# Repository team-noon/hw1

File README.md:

# Hardware 1
The first hardware design of our team

> [!WARNING]
> still under development!

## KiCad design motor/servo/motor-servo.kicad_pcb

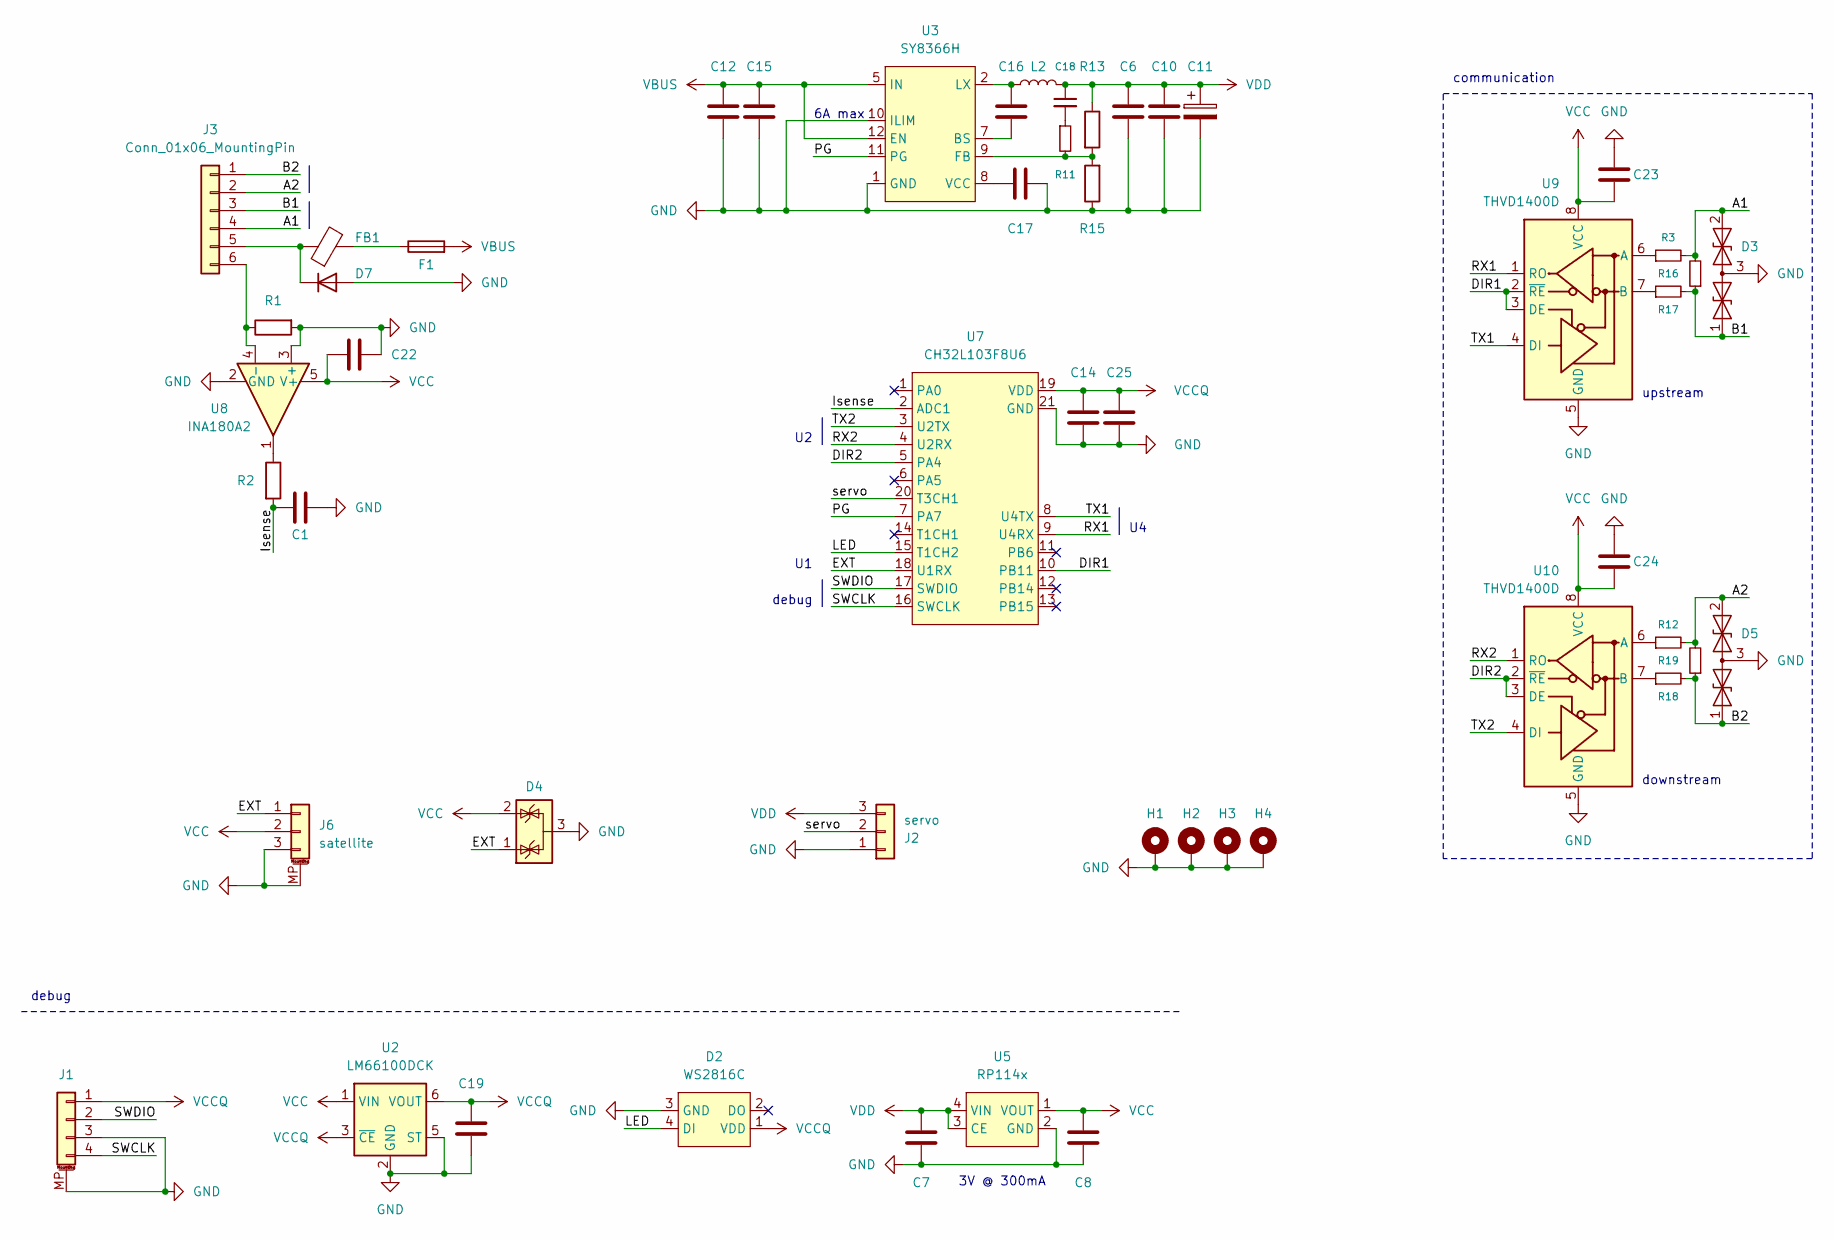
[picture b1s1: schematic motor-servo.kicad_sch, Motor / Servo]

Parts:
C1: 100n
C6, C10: 22u; C_0805_2012Metric; LCSC C98190
C7, C8: 1u; C_0402_1005Metric; LCSC C7001784
C11: 220u; CP_Elec_6.3x5.4; LCSC C2977551
C12: 10u (HV); C_0805_2012Metric
C14: 100n; C_0402_1005Metric; LCSC C77020
C15: 1u (HV); C_0603_1608Metric; LCSC C307331
C16: 100n; C_0402_1005Metric; LCSC C60474
C17: 2.2u; C_0402_1005Metric; LCSC C12530
C18: 22p; C_0402_1005Metric; LCSC C106203
C19: 10u; C_0402_1005Metric; LCSC C315248
C22, C23, C24: 100n; C_0402_1005Metric
C25: 2.2u; C_0402_1005Metric; LCSC C77020
D2: WS2816C; WS2816C-1313-4P; LCSC C42417612
D3, D5: SM712_SOT23; SOT-23; LCSC C404012
D4: NUP1303; SOT-23; LCSC C2831529
D7: D; D_SOD-123F; LCSC C19077515
F1: 8A; Fuse_1206_3216Metric; LCSC C41367232
FB1: FerriteBead; L_0805_2012Metric; LCSC C596496
H1, H2, H3, H4: MountingHole_Pad; MountingHole_2.2mm_M2_DIN965_Pad
J1: DEBUG; JST_SH_BM04B-SRSS-TB_1x04-1MP_P1.00mm_Vertical; LCSC C160390
J2: servo; Molex_Micro-Fit_3.0_43650-0300_1x03_P3.00mm_Horizontal; LCSC C503478
J3: Conn_01x06_MountingPin; Molex_Micro-Fit_3.0_43650-0600_1x06_P3.00mm_Horizontal; LCSC C492352
J6: satellite; JST_SH_SM03B-SRSS-TB_1x03-1MP_P1.00mm_Horizontal; LCSC C160403
L2: 2u; 0630CDMCD_DS; LCSC C2453290
R1: 10m; R_1206_3216Metric; LCSC C7467248
R2: 100
R3, R12, R16, R17, R18, R19: R_Small; R_0402_1005Metric
R11: 150k; R_0402_1005Metric
R13: 100k; R_0402_1005Metric
R15: 13k; R_0402_1005Metric
U2: LM66100DCK; SOT-363_SC-70-6; LCSC C2869734
U3: SY8366H; QFN3x3-12; LCSC C178253
U5: RP114x; UDFN-4-1EP_1x1mm_P0.65mm_EP0.48x0.48mm; LCSC C194610
U7: CH32L103F8U6; VQFN-20-1EP_3x3mm_P0.4mm_EP1.7x1.7mm; LCSC C22467836
U8: INA180A2; SOT-23-5; LCSC C192764
U9, U10: THVD1400D; SOT-583-8; LCSC C3235289

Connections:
/A1: D3.2 (A2), J3.4, R3.2, R16.2
/A2: D5.2 (A2), J3.2, R12.2, R19.2
/B1: D3.1 (A1), J3.3, R16.1, R17.2
/B2: D5.1 (A1), J3.1, R18.2, R19.1
/DIR1: U7.10 (PB11), U9.2 (~RE), U9.3 (DE)
/DIR2: U7.5 (PA4), U10.2 (~RE), U10.3 (DE)
/EXT: D4.1 (K), J6.1, U7.18 (U1RX)
/Isense: C1.1, R2.2, U7.2 (ADC1)
/LED: D2.4 (DI), U7.15 (T1CH2)
/PG: U3.11 (PG), U7.7 (PA7)
/RX1: U7.9 (U4RX), U9.1 (RO)
/RX2: U7.4 (U2RX), U10.1 (RO)
/SWCLK: J1.4, U7.16 (SWCLK)
/SWDIO: J1.2, U7.17 (SWDIO)
/TX1: U7.8 (U4TX), U9.4 (DI)
/TX2: U7.3 (U2TX), U10.4 (DI)
/servo: J2.2, U7.20 (T3CH1)
GND: C1.2, C6.2, C7.2, C8.2, C10.2, C11.2, C12.2, C14.2, C15.2, C17.2, C19.2, C22.2, C23.1, C24.1, C25.2, D2.3 (GND), D3.3 (common), D4.3 (A), D5.3 (common), D7.2 (A), H1.1 (1_1), H2.1 (1_1), H3.1 (1_1), H4.1 (1_1), J1.3, J1.MP (MountPin), J2.1, J6.3, J6.MP (MountPin), R1.2, R15.1, U2.2 (GND), U2.5 (ST), U3.1 (GND), U3.10 (ILIM), U5.2 (GND), U5.5 (EP), U7.21 (GND), U8.2 (GND), U8.3 (+), U9.5 (GND), U10.5 (GND)
unnamed: C18.2, R11.1
unnamed: D7.1 (K), FB1.1, J3.5
unnamed: F1.1, FB1.2
unnamed: J3.6, R1.1, U8.4 (-)
unnamed: R2.1, U8.1
unnamed: C16.1, U3.7 (BS)
unnamed: R11.2, R13.2, R15.2, U3.9 (FB)
unnamed: C16.2, L2.1, U3.2 (LX)
unnamed: C17.1, U3.8 (VCC)
unnamed: R3.1, U9.6 (A)
unnamed: R17.1, U9.7 (B)
unnamed: R12.1, U10.6 (A)
unnamed: R18.1, U10.7 (B)
VBUS: C12.1, C15.1, F1.2, U3.5 (IN), U3.6 (IN), U3.12 (EN)
VCC: C8.1, C22.1, C23.2, C24.2, D4.2 (K), J6.2, U2.1 (VIN), U5.1 (VOUT), U8.5 (V+), U9.8 (VCC), U10.8 (VCC)
VCCQ: C14.1, C19.1, C25.1, D2.1 (VDD), J1.1, U2.3 (~CE), U2.6 (VOUT), U7.19 (VDD)
VDD: C6.1, C7.1, C10.1, C11.1, C18.1, J2.3, L2.2, R13.1, U5.3 (CE), U5.4 (VIN)

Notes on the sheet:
3V @ 300mA
downstream
debug
6A max
upstream
communication

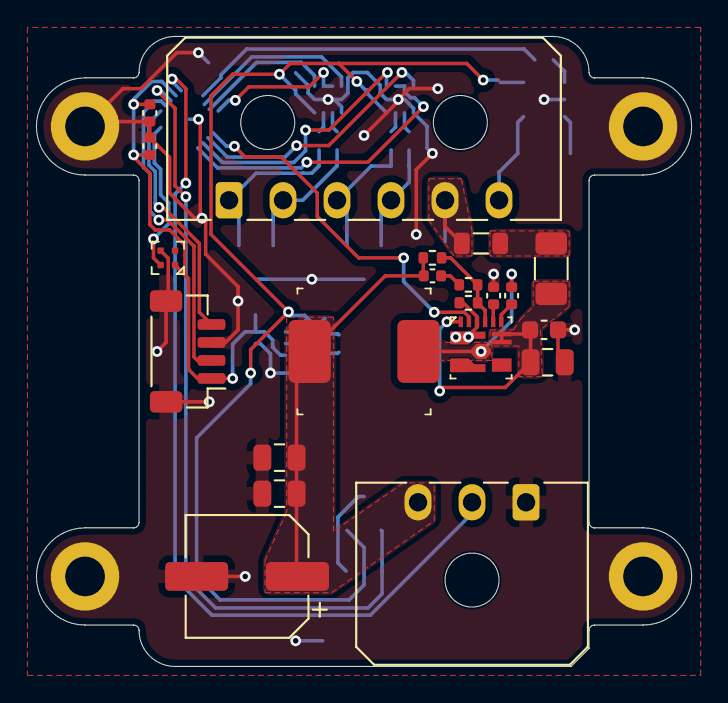
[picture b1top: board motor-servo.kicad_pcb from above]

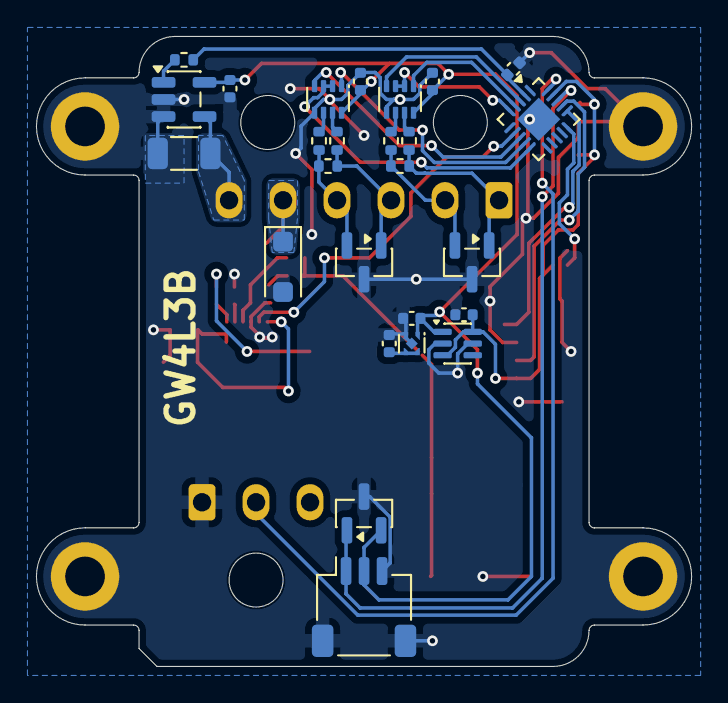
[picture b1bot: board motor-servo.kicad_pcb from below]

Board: 2 copper layers, 36.4 x 35.0 mm, 51 parts (26 on the bottom side), 35 nets.

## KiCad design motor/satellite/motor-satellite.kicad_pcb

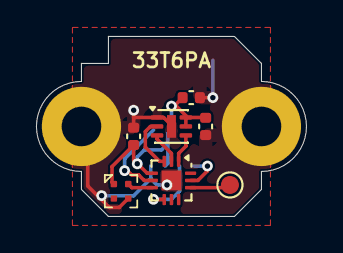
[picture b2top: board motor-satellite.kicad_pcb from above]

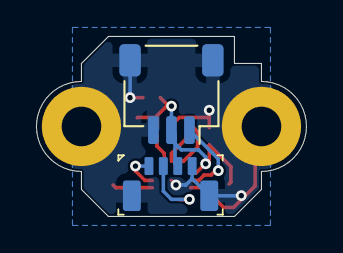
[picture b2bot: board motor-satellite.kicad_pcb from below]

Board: 2 copper layers, 15.0 x 10.0 mm, 11 parts (2 on the bottom side), 10 nets.

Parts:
C1, C2: 100n; C_0402_1005Metric
C3: 10u; C_0402_1005Metric
D2: WS2816C; WS2816C-1313-4P
H1, H2: MountingScrew; MountingHole_2.2mm_M2_Pad
J3: Conn_01x04_MountingPin; HC-0.8-4PWT
J6: Conn_01x03_MountingPin; JST_SH_SM03B-SRSS-TB_1x03-1MP_P1.00mm_Horizontal
TP1: SWIO; TestPoint_Pad_D1.0mm
U1: CH32V005D6U6; UQFN-12-1EP_2x2mm_P0.4mm_EP1.1x1.1mm
U3: SC4251; MLF-6-1EP_1.6x1.6mm_P0.5mm_EP0.5x1.26mm

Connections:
/A0: J3.2, U1.7 (PC4)
/A1: J3.1, U1.11 (PD4)
/LED: D2.4 (DI), U1.6 (PC3)
/PX: U1.2 (PA2), U3.3 (OUTx)
/PY: U1.1 (PA1), U3.4 (OUTy)
/SLEEP: U1.3 (PD0), U3.2 (SLEEP)
/TX: J6.1, U1.5 (PC0)
GND: C1.2, C2.2, C3.2, D2.3 (GND), H1.1 (PAD_1), H2.1 (PAD_1), J3.4, J3.MP (MountPin), J6.3, J6.MP (MountPin), U1.13 (VSS), U3.1 (GND), U3.7 (EP)
unnamed: TP1.1 (1_1), U1.10 (SWIO)
VCC: C1.1, C2.1, C3.1, D2.1 (VDD), J3.3, J6.2, U1.4 (VDD), U3.5 (GAIN), U3.6 (VCC)

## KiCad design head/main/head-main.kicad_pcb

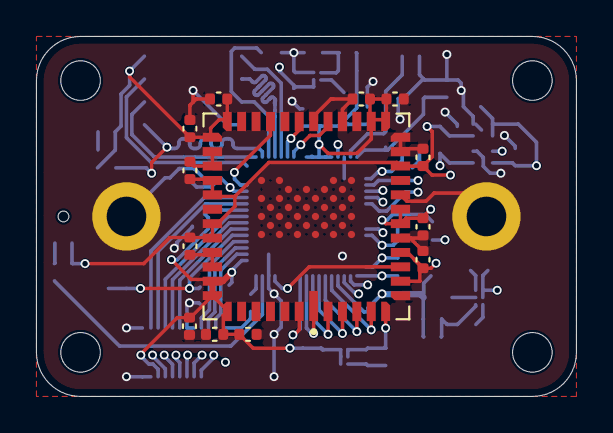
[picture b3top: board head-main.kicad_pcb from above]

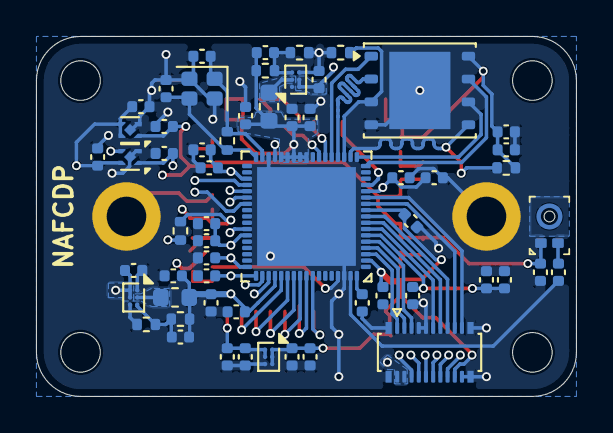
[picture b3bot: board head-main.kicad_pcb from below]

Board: 4 copper layers, 30.0 x 20.0 mm, 77 parts (60 on the bottom side), 48 nets.

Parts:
C1, C2, C3, C4, C8, C9, C11, C15, C19, C22, C24, C27, C29, C31, C41, C43: 0.1u; C_0402_1005Metric
C5, C32, C39, C40, C60, C61, C65: 10u; C_0402_1005Metric
C6, C17, C20, C23, C33, C34, C37: 2.2u; C_0402_1005Metric
C7, C10, C26, C28, C30, C35, C36, C42, C50, C53, C54, C55: 1u; C_0402_1005Metric
C14: 100n; C_0402_1005Metric
C21, C25: 18p; C_0402_1005Metric
C51, C52: 4.7u; C_0402_1005Metric
C57: 47p; C_0402_1005Metric
C58: 33p; C_0402_1005Metric
C63: 4.7u (Cin); C_0402_1005Metric
H1, H2, H3, H4: MountingHole_Pad; MountingHole_2.2mm_M2
H5, H6: MountingHole_Pad; MountingHole_2.2mm_M2_DIN965_Pad
J1: conn_head_comms; Hirose_DF40C-20DP-0.4V_2x10-1MP_P0.4mm
L1, L2: 0.47u; L_0603_1608Metric
R1: 10k; R_0402_1005Metric
R3: 1M; R_0402_1005Metric
R4, R5: 4.7k; R_0402_1005Metric
R6, R7: 220k; R_0402_1005Metric
R9: 110k; R_0402_1005Metric
R10: 440k; R_0402_1005Metric
U1: CV1800B; ArtInChip_QFN-68-1EP_7x7mm_P0.35mm_EP5.49x5.49mm
U2: AR0237CS; PLCC-48-11.43x11.4mm
U3: GTA2718B-3HA
U4: W25Q128JVP; WSON-8-1EP_6x5mm_P1.27mm_EP3.4x4.3mm
U5, U6: RP509x; WLCSP-6_1.4x1.0mm_P0.4mm
U7: RP114x; UDFN-4-1EP_1x1mm_P0.65mm_EP0.48x0.48mm
U8: LP3982S; UDFN-4-1EP_1x1mm_P0.65mm_EP0.48x0.48mm
U9: NCP136; WLCSP-6_1.4x1.0mm_P0.4mm
Y1: 25M; Crystal_SMD_2016-4Pin_2.0x1.6mm

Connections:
+1V8: C1.1, C2.1, C4.1, C5.1, C6.1, C9.1, C10.1, C11.1, C14.1, C27.1, C31.1, C32.1, C34.1, C35.1, C37.1, C41.2, C58.2, C61.1, C63.1, J1.18, L2.2, R1.2, R4.2, R10.2, U1.2 (VDD18A_AUD), U1.10 (VDDIO_SD0_SPI), U1.26 (VDDQ), U1.27 (VDDQ), U1.28 (VDDQ), U1.29 (VDDIO_RTC), U1.30 (PWR_VBAT_DET), U1.52 (VDD18A_USB_PLL_ETH_CSI), U2.12 (VDDIO), U2.13 (VDD), U2.19 (VDD), U2.20 (VDDIO), U2.30 (VDDIO), U2.31 (VDD), U2.41 (VDD), U2.42 (VDDIO), U2.43 (VDD1V8_PHY), U4.8 (VCC), U9.A1 (IN), U9.B1 (EN), U9.C1 (BIAS)
+2V8: C26.1, C28.1, C30.1, C36.1, C43.1, C55.1, U2.8 (VDD_PLL), U2.10 (VAA), U2.16 (VAA), U2.34 (VAA_PIX), U2.35 (VAA), U2.37 (VAA), U2.38 (VAA_PIX), U3.1 (VDD), U8.1 (VOUT)
+3V3: C3.1, C53.1, U1.51 (VD33A_ETH_USB_SD1), U7.1 (VOUT)
+5V: C50.1, C51.1, C52.1, C54.1, J1.2, J1.4, U5.A2 (VIN), U5.B2 (CE), U6.A2 (VIN), U6.B2 (CE), U7.4 (VIN), U8.3 (EN), U8.4 (VIN)
/0V4: C29.2, C65.1, U2.6 (VDD_SLVS), U9.A2 (OUT), U9.B2 (SNS)
/0V9: C8.1, C15.1, C17.1, C19.1, C20.1, C22.1, C23.1, C24.1, C33.1, C39.1, C40.1, C57.2, C60.1, L1.2, R9.2, U1.6 (VDDC), U1.13 (VDDC), U1.37 (VDDC), U1.46 (VDDC), U1.55 (VDDC)
/CAM_CLK: U1.65 (MIPIRX0P), U2.9 (EXTCLK)
/CAM_OE: U1.14 (SPK_EN), U2.27 (OE_N)
/CAM_SCL: U1.23 (IIC0_SCL), U2.25 (SCL)
/CAM_SDA: U1.24 (IIC0_SDA), U2.23 (SDA)
/LED: J1.10, U1.41 (SD1_D0)
/MCN: U1.60 (MIPIRX2N), U2.1 (SLVSLCN)
/MCP: U1.61 (MIPIRX2P), U2.48 (SLVSLCP)
/MDN0: U1.56 (MIPIRX4N), U2.5 (SLVS0N)
/MDN1: U1.58 (MIPIRX3N), U2.3 (SPVS1N)
/MDP0: U1.57 (MIPIRX4P), U2.4 (SLVS0P)
/MDP1: U1.59 (MIPIRX3P), U2.2 (SLVS1P)
/MIC: C42.2, U3.2 (Out)
/NOR_CS: U1.22 (SPINOR_CS_X), U4.1 (~CS)
/NOR_HOLD: U1.17 (SPINOR_HOLD_X), U4.7 (~HOLD/~RESET/IO_{3})
/NOR_MISO: U1.21 (SPINOR_MISO), U4.2 (DO/IO_{1})
/NOR_MOSI: R4.1, U1.19 (SPINOR_MOSI), U4.5 (DI/IO_{0})
/NOR_SCK: U1.18 (SPINOR_SCK), U4.6 (CLK)
/NOR_WP: R5.1, U1.20 (SPINOR_WP_X), U4.3 (~WP/IO_{2})
/PWRSEQ: U1.31 (PWR_SEQ2), U7.3 (CE)
/U3RX: J1.12, U1.40 (SD1_D1)
/U3TX: J1.14, U1.39 (SD1_D2)
/UDIR: J1.16, U1.38 (SD1_D3)
/USB_DM: J1.6, U1.54 (USB_DM)
/USB_DP: J1.8, U1.53 (USB_DP)
/WIFI_CLK: J1.1, U1.3 (SD0_CLK)
/WIFI_CMD: J1.3, U1.4 (SD0_CMD)
/WIFI_D0: J1.5, U1.5 (SD0_D0)
/WIFI_D1: J1.11, U1.7 (SD0_D1)
/WIFI_D2: J1.13, U1.8 (SD0_D2)
/WIFI_D3: J1.15, U1.9 (SD0_D3)
/WIFI_EN: J1.19, U1.12 (SD0_PWR_EN)
/WIFI_INT: J1.17, U1.11 (SD0_CD)
/XIN: C25.2, R3.1, U1.33 (XTAL_XIN), Y1.1
/XOUT: C21.2, R3.2, U1.34 (XTAL_XOUT), Y1.3
GND: C1.2, C2.2, C3.2, C4.2, C5.2, C6.2, C7.2, C8.2, C9.2, C10.2, C11.2, C14.2, C15.2, C17.2, C19.2, C20.2, C21.1, C22.2, C23.2, C24.2, C25.1, C26.2, C27.2, C28.2, C29.1, C30.2, C31.2, C32.2, C33.2, C34.2, C35.2, C36.2, C37.2, C39.2, C40.2, C41.1, C43.2, C50.2, C51.2, C52.2, C53.2, C54.2, C55.2, C60.2, C61.2, C63.2, C65.2, H5.1 (1_1), H6.1 (1_1), J1.7, J1.9, J1.20, J1.MP (MountPin), R5.2, R6.1, R7.1, U1.32 (PTEST), U1.66 (VSS18A_AUD), U1.69 (VSSC), U2.7 (DGND), U2.11 (AGND), U2.14 (DGND), U2.17 (AGND), U2.18 (DGND), U2.22 (TEST), U2.24 (SADDR), U2.32 (DGND), U2.33 (AGND), U2.39 (AGND), U2.40 (DGND), U2.49 (DGND), U3.3 (GND), U4.4 (GND), U4.9 (EP), U5.A1 (MODE), U5.C2 (GND), U6.A1 (MODE), U6.C2 (GND), U7.2 (GND), U7.5 (TP), U8.2 (GND), U8.5 (TP), U9.C2 (GND), Y1.2 (G), Y1.4 (G)
unnamed: R1.1, U1.45 (USB_VBUS_DET)
unnamed: C42.1, U1.67 (PAD_AUD_AINL_MIC)
unnamed: C7.1, U1.68 (PAD_AUD_AVREF)
unnamed: L1.1, U5.B1 (LX)
unnamed: C57.1, R6.2, R9.1, U5.C1 (VFB)
unnamed: L2.1, U6.B1 (LX)
unnamed: C58.1, R7.2, R10.1, U6.C1 (VFB)

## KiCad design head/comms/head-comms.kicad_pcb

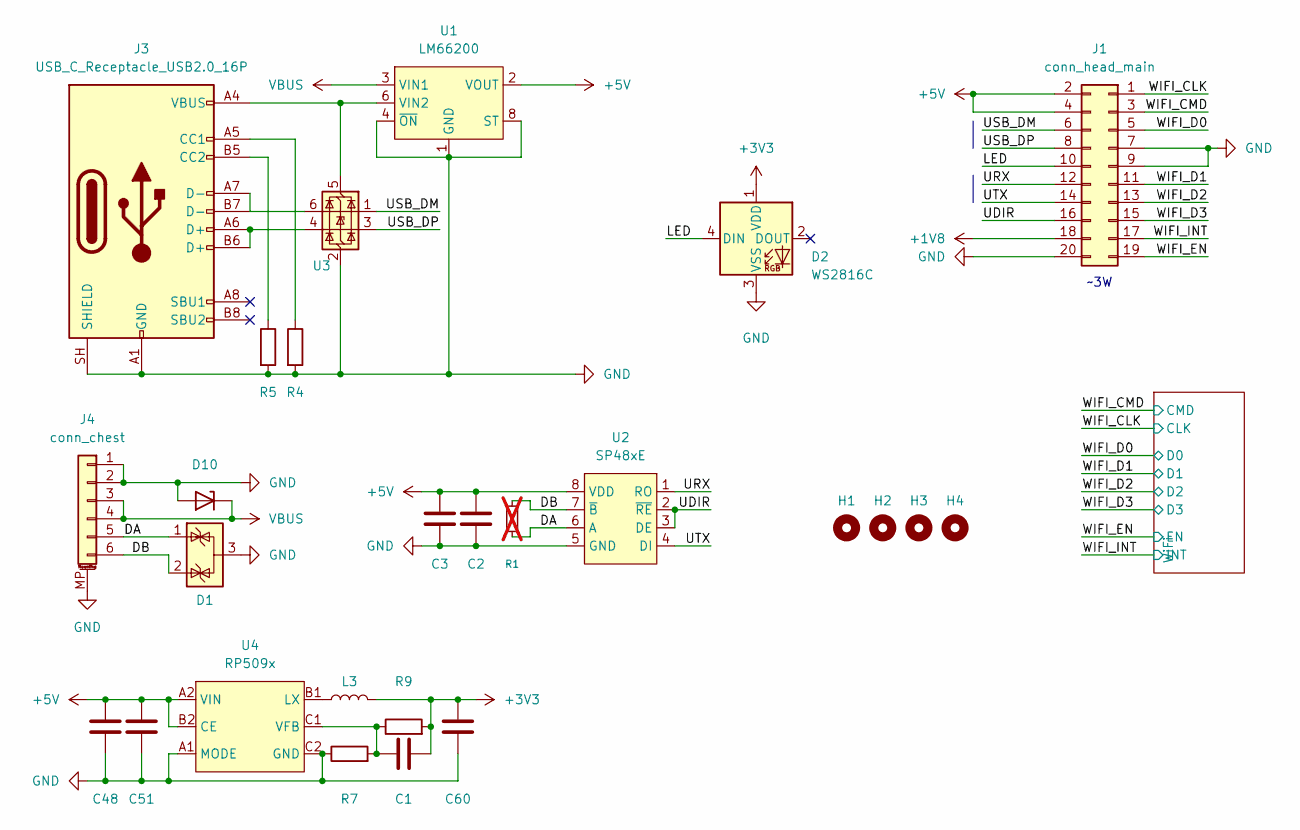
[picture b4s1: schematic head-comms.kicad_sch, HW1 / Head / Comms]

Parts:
C1: 6.8p; C_0402_1005Metric; LCSC *
C2: 100n; C_0402_1005Metric; LCSC *
C3, C51: 4.7u; C_0402_1005Metric; LCSC *
C48, C60: 10u; C_0402_1005Metric; LCSC *
D1: SZNUP2105L; SOT-23; LCSC C233494
D2: WS2816C; WS2816C-1313-4P; LCSC C42417612
D10: ESD5Zxx; D_SOD-523; LCSC C82323
H1, H2, H3, H4: MountingHole_Pad; MountingHole_2.2mm_M2
J1: conn_head_main; Hirose_DF40C-20DS-0.4V_2x10_P0.4mm; LCSC C3644774
J3: USB_C_Receptacle_USB2.0_16P; USB_C_Receptacle_HRO_TYPE-C-31-M-12; LCSC C165948
J4: conn_chest; JST_SH_SM06B-SRSS-TB_1x06-1MP_P1.00mm_Horizontal; LCSC C160405
L3: 0.47u; L_0603_1608Metric; LCSC C882988
R1: 120; R_0402_1005Metric; not fitted
R4, R5: 5.1k; R_0402_1005Metric; LCSC *
R7: 47k; R_0402_1005Metric; LCSC *
R9: 211.5k; R_0402_1005Metric; LCSC *
U1: LM66200; SOT-583-8; LCSC C3235556
U2: SP48xE; SOIC-8_3.9x4.9mm_P1.27mm; LCSC C6855
U3: USBLC6-2SC6; SOT-23-6; LCSC C2687116
U4: RP509x; WLCSP-6_1.4x1.0mm_P0.4mm; LCSC C3194629

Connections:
+1V8: J1.18; also elsewhere on the board
+3V3: C1.2, C60.1, D2.1 (VDD), L3.2, R9.2; also elsewhere on the board
+5V: C2.1, C3.1, C48.1, C51.1, J1.2, J1.4, U1.2 (VOUT), U1.7 (VOUT), U2.8 (VDD), U4.A2 (VIN), U4.B2 (CE)
/DA: D1.1 (K), J4.5, R1.2, U2.6 (A)
/DB: D1.2 (K), J4.6, R1.1, U2.7 (~B)
/LED: D2.4 (DIN), J1.10
/UDIR: J1.16, U2.2 (~RE), U2.3 (DE)
/URX: J1.12, U2.1 (RO)
/USB_DM: J1.6, U3.1 (I/O1)
/USB_DP: J1.8, U3.3 (I/O2)
/UTX: J1.14, U2.4 (DI)
/WIFI_CLK: J1.1; also elsewhere on the board
/WIFI_CMD: J1.3; also elsewhere on the board
/WIFI_D0: J1.5; also elsewhere on the board
/WIFI_D1: J1.11; also elsewhere on the board
/WIFI_D2: J1.13; also elsewhere on the board
/WIFI_D3: J1.15; also elsewhere on the board
/WIFI_EN: J1.19; also elsewhere on the board
/WIFI_INT: J1.17; also elsewhere on the board
GND: C2.2, C3.2, C48.2, C51.2, C60.2, D1.3 (A), D2.3 (VSS), D10.2 (A), J1.7, J1.9, J1.20, J3.A1 (GND), J3.A12 (GND), J3.B1 (GND), J3.B12 (GND), J3.SH (SHIELD), J4.1, J4.2, J4.MP (MountPin), R4.2, R5.2, R7.1, U1.1 (GND), U1.4 (~ON), U1.5 (GND), U1.8 (ST), U2.5 (GND), U3.2 (GND), U4.A1 (MODE), U4.C2 (GND); also elsewhere on the board
unnamed: J3.A5 (CC1), R4.1
unnamed: J3.B5 (CC2), R5.1
unnamed: J3.A6 (D+), J3.B6 (D+), U3.4 (I/O2)
unnamed: J3.A7 (D-), J3.B7 (D-), U3.6 (I/O1)
unnamed: J3.A4 (VBUS), J3.A9 (VBUS), J3.B4 (VBUS), J3.B9 (VBUS), U1.6 (VIN2), U3.5 (VBUS)
unnamed: L3.1, U4.B1 (LX)
unnamed: C1.1, R7.2, R9.1, U4.C1 (VFB)
VBUS: D10.1 (K), J4.3, J4.4, U1.3 (VIN1)

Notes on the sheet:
~3W

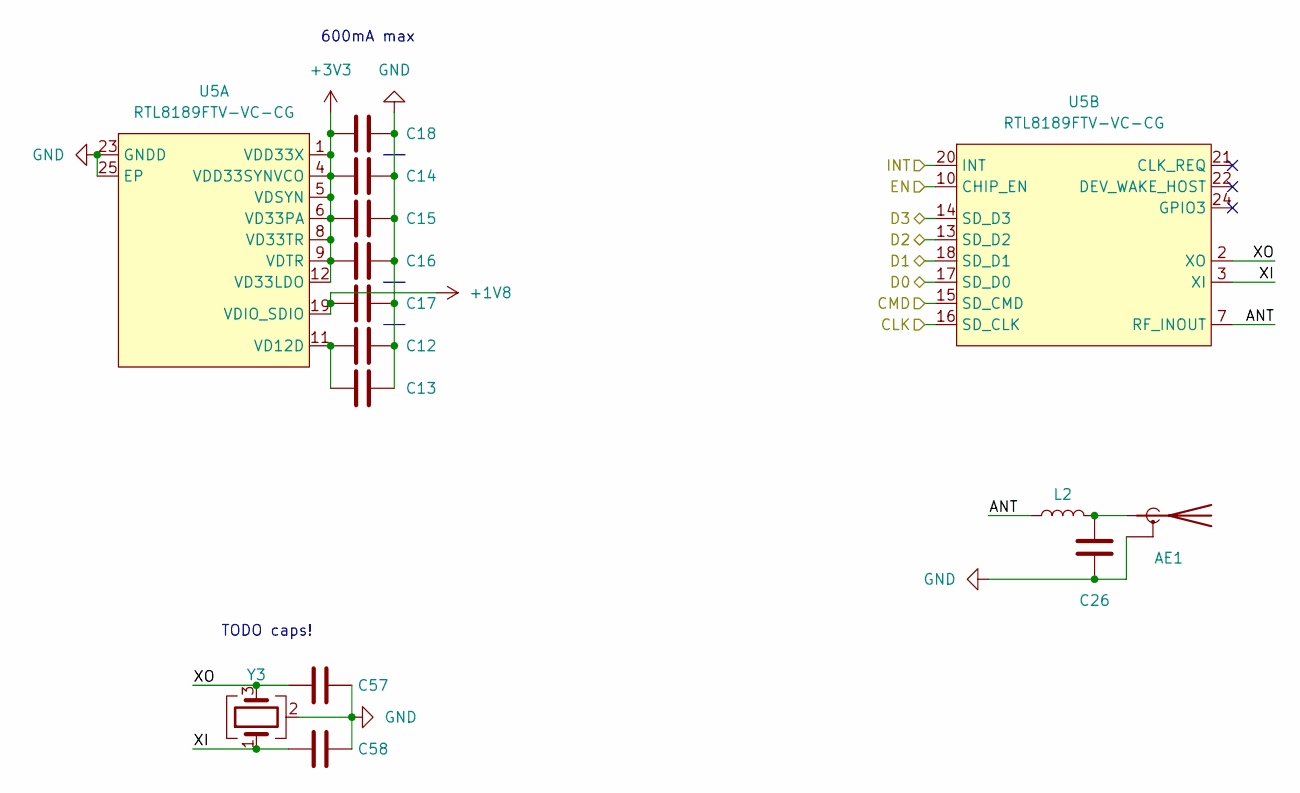
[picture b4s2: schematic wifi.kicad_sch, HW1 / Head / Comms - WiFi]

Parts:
AE1: Antenna_Shield; Texas_SWRA117D_2.4GHz_Left
C12, C14, C15, C16, C17, C18: 100n; C_0402_1005Metric; LCSC *
C13: 4.7u; C_0402_1005Metric; LCSC *
C26: DNF; C_0402_1005Metric
C57, C58: 10p; C_0402_1005Metric; LCSC *
L2: 0; L_0402_1005Metric; LCSC C2906877
U5: RTL8189FTV-VC-CG; HVQFN-24-1EP_4x4mm_P0.5mm_EP2.1x2.1mm; LCSC C2687145
Y3: 26M; Crystal_SMD_2016-4Pin_2.0x1.6mm; LCSC C37635330

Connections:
+1V8: C17.1, U5.19 (VDIO_SDIO); also elsewhere on the board
+3V3: C14.1, C15.1, C16.1, C18.1, U5.1 (VDD33X), U5.4 (VDD33SYNVCO), U5.5 (VDSYN), U5.6 (VD33PA), U5.8 (VD33TR), U5.9 (VDTR), U5.12 (VD33LDO); also elsewhere on the board
/WIFI_CLK: U5.16 (SD_CLK); also elsewhere on the board
/WIFI_CMD: U5.15 (SD_CMD); also elsewhere on the board
/WIFI_D0: U5.17 (SD_D0); also elsewhere on the board
/WIFI_D1: U5.18 (SD_D1); also elsewhere on the board
/WIFI_D2: U5.13 (SD_D2); also elsewhere on the board
/WIFI_D3: U5.14 (SD_D3); also elsewhere on the board
/WIFI_EN: U5.10 (CHIP_EN); also elsewhere on the board
/WIFI_INT: U5.20 (INT); also elsewhere on the board
/WiFi/ANT: L2.1, U5.7 (RF_INOUT)
/WiFi/XI: C58.1, U5.3 (XI), Y3.1
/WiFi/XO: C57.1, U5.2 (XO), Y3.3
GND: AE1.2 (Shield), C12.2, C13.2, C14.2, C15.2, C16.2, C17.2, C18.2, C26.2, C57.2, C58.2, U5.23 (GNDD), U5.25 (EP), Y3.2 (G), Y3.4 (G); also elsewhere on the board
unnamed: AE1.1 (A), C26.1, L2.2
unnamed: C12.1, C13.1, U5.11 (VD12D)

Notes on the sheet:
600mA max
TODO caps!

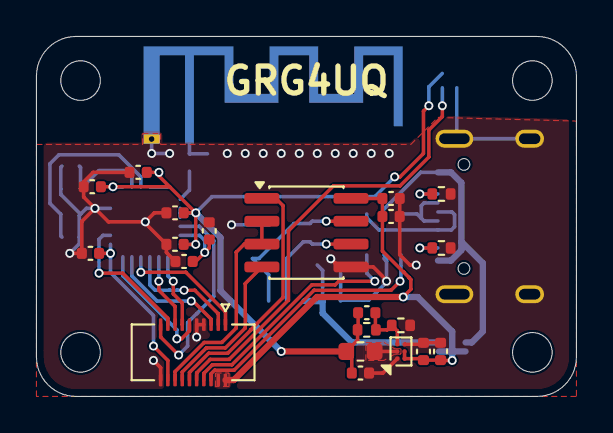
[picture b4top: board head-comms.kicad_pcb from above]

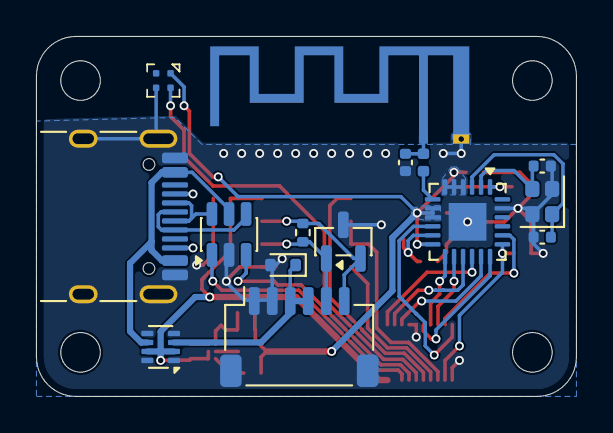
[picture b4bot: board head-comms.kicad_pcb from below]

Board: 2 copper layers, 30.0 x 20.0 mm, 40 parts (15 on the bottom side), 33 nets.

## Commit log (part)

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2026-01-14 head_a
2026-04-26 implement head/main
2026-04-26 update title
2026-04-26 update communication pinout
2026-04-26 implement head/comms
2026-04-26 finishing touches
2026-04-26 fix missing ESD diode
2026-04-28 larger traces
2026-04-28 larger traces, swapped connector
2026-04-28 move connector, cleanup traces
2026-04-28 cleanup traces
2026-04-28 first finished iteratin
2026-04-28 implement driver
